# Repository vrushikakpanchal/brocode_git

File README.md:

# UnPlugged 2.0 - Smart City Sentinel

## Overview
This project was developed as part of **UnPlugged 2.0**, a 24-hour hardware hackathon organized by Shri Vile Parle Kelavani Mandal's Dwarkadas J. Sanghvi College of Engineering. Our solution focuses on **AI-driven IoT & GIS-based urban intelligence** to optimize traffic management, environmental monitoring, and public safety.

## Problem Statement
With rapid urbanization, cities face challenges in managing infrastructure, optimizing resources, and ensuring public safety. Existing systems often react too slowly, leading to inefficiencies. Our task was to **engineer an autonomous system** integrating:
- **IoT-based urban monitoring**
- **Multi-sensor data fusion**
- **Geographic Information System (GIS)**
- **AI models for traffic control, emergency response, and environmental monitoring**
- **Decentralized edge AI for real-time decision-making**

## Solution Implemented
### **1. Traffic Flow Optimization** 🚦
- **ESP32 cameras** placed across **4 lanes** to monitor vehicle density.
- AI logic to **prioritize lane clearance** based on congestion levels.

### **2. Environmental Monitoring** 🌍
- Hardware setup includes sensors for **AQI, dust, and temperature levels**.
- Data is **transmitted in real-time** to a **cloud-based dashboard**.

### **3. User Dashboard & Access** 🖥️
- **Two types of logins:**
  - **Admin (Traffic Police):** Controls signal timings.
  - **User:** Accesses live traffic updates and environmental data.
- **Web-based dashboard** for real-time monitoring.

## Tech Stack & Components
- **Hardware:** ESP32-CAM, air quality sensors, temperature sensors, solar-powered PCB
- **Software:** KiCad (PCB design), Python, Flask, React.js
- **Cloud & AI:** Firebase, Edge AI for anomaly detection

## Team Members 👥
- Vrushika Panchal [Diploma - AI/ML]
- Harsh Pandey [B.Tech - EXTC]
- Soham Nagvekar [B.Tech - EXTC]
- Prasad Rane [B.Tech - EXTC]
- Atharva Wadekar [B.Tech - EXTC]
- Advait Shinde [Diploma - AI/ML]

## Repository Structure
```
📂 brocode_git
 ┣ 📂 01_Kicad_PCB        # KiCad PCB designs
 ┣ 📂 02_GERBER           # ESP32 & IoT sensor integration
 ┣ 📂 03_project_images           # React.js frontend for monitoring
 ┣ 📂 04_frontend_website               # Traffic analysis & anomaly detection
 ┣ 📜 README.md               # Project documentation
```

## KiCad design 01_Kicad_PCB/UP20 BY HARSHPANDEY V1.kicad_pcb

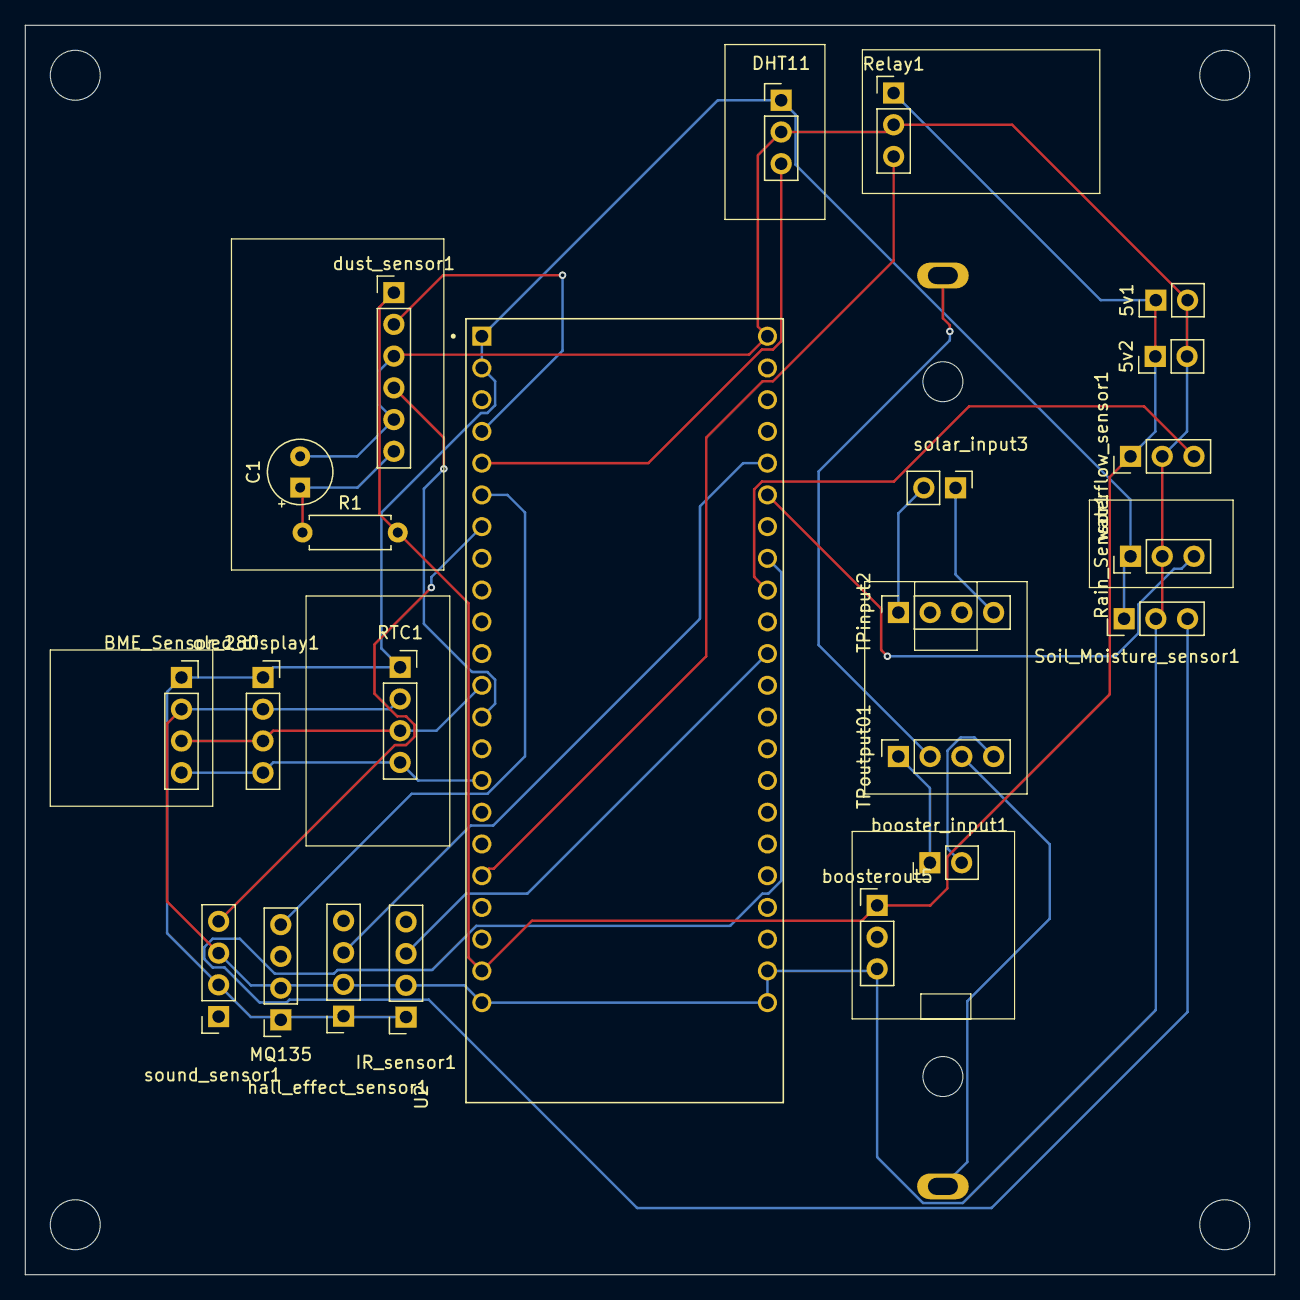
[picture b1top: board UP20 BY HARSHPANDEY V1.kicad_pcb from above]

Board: 2 copper layers, 100.0 x 100.0 mm, 24 parts (1 on the bottom side), 23 nets.

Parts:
5v1, 5v2: Conn_01x02_Pin; PinHeader_1x02_P2.54mm_Vertical
BME_Sensor_280: Conn_01x04_Pin; PinSocket_1x04_P2.54mm_Vertical
BT2: BK-18650-PC2; BAT_BK-18650-PC2
C1: C_Polarized; CP_Radial_Tantal_D5.0mm_P2.50mm
DHT11: Conn_01x03_Pin; PinHeader_1x03_P2.54mm_Vertical
IR_sensor1: Conn_01x04_Pin; PinSocket_1x04_P2.54mm_Vertical
MQ135: Conn_01x04_Pin; PinSocket_1x04_P2.54mm_Vertical
R1: R; R_Axial_DIN0207_L6.3mm_D2.5mm_P7.62mm_Horizontal
RTC1: Conn_01x04_Pin; PinSocket_1x04_P2.54mm_Vertical
Rain_Sensor1: Conn_01x03_Pin; PinHeader_1x03_P2.54mm_Vertical
Relay1: Conn_01x03_Pin; PinHeader_1x03_P2.54mm_Vertical
Soil_Moisture_sensor1: Conn_01x03_Pin; PinHeader_1x03_P2.54mm_Vertical
TPinput2: Conn_01x04_Pin; PinSocket_1x04_P2.54mm_Vertical
TPoutput01: Conn_01x04_Pin; PinSocket_1x04_P2.54mm_Vertical
U2: ESP32-S3-DEVKITC-1-N8R2; XCVR_ESP32-S3-DEVKITC-1-N8R2
booster_input1: Conn_01x02_Pin; PinHeader_1x02_P2.54mm_Vertical
boosterout5: Conn_01x03_Pin; PinHeader_1x03_P2.54mm_Vertical
dust_sensor1: Conn_01x06_Pin; PinHeader_1x06_P2.54mm_Vertical
hall_effect_sensor1: Conn_01x04_Pin; PinSocket_1x04_P2.54mm_Vertical
oled_display1: Conn_01x04_Pin; PinSocket_1x04_P2.54mm_Vertical
solar_input3: Conn_01x02_Pin; PinHeader_1x02_P2.54mm_Vertical
sound_sensor1: Conn_01x04_Pin; PinSocket_1x04_P2.54mm_Vertical
waterflow_sensor1: Conn_01x03_Pin; PinHeader_1x03_P2.54mm_Vertical

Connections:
3.3V: BME_Sensor_280.1, DHT11.1, IR_sensor1.1, MQ135.1, RTC1.1, Rain_Sensor1.1, Soil_Moisture_sensor1.1, U2.J1_1 (3V3), U2.J1_2 (3V3), hall_effect_sensor1.1, oled_display1.1, sound_sensor1.2
5V: 5v1.1, 5v2.1, R1.2, Relay1.1, U2.J1_21 (5V0), boosterout5.1, dust_sensor1.1, waterflow_sensor1.1
GND: 5v1.2, 5v2.2, BME_Sensor_280.2, C1.2, DHT11.2, IR_sensor1.2, MQ135.2, RTC1.2, Rain_Sensor1.2, Relay1.2, Soil_Moisture_sensor1.2, U2.J1_22 (GND), U2.J3_1 (GND), U2.J3_21 (GND), U2.J3_22 (GND), boosterout5.3, dust_sensor1.3, dust_sensor1.5, hall_effect_sensor1.2, oled_display1.2, sound_sensor1.3, waterflow_sensor1.2
unnamed: DHT11.3, U2.J1_5 (GPIO5)
unnamed: IR_sensor1.3, U2.J3_11 (GPIO37)
unnamed: MQ135.4, U2.J1_6 (GPIO6)
unnamed: Rain_Sensor1.3, U2.J3_6 (MTMS/GPIO42)
unnamed: Relay1.3, U2.J1_18 (GPIO12)
unnamed: Soil_Moisture_sensor1.3, U2.J3_8 (MTDO/GPIO40)
unnamed: TPinput2.1, solar_input3.2
unnamed: TPinput2.4, solar_input3.1
unnamed: TPoutput01.1, booster_input1.1
unnamed: BT2.+, TPoutput01.2
unnamed: BT2.-, TPoutput01.3
unnamed: TPoutput01.4, booster_input1.2
unnamed: U2.J3_5 (GPIO2), hall_effect_sensor1.3
unnamed: U2.J1_13 (GPIO3), dust_sensor1.4
unnamed: U2.J1_4 (GPIO4), dust_sensor1.2
unnamed: U2.J1_7 (GPIO7), sound_sensor1.4
unnamed: U2.J3_9 (MTCK/GPIO39), waterflow_sensor1.3
unnamed: C1.1, R1.1, dust_sensor1.6
SCL: BME_Sensor_280.4, RTC1.4, U2.J1_15 (GPIO9), oled_display1.4
SDA: BME_Sensor_280.3, RTC1.3, U2.J1_12 (GPIO8), oled_display1.3

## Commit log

2025-03-11 Removed all existing files
2025-03-11 Ignore large video files
2025-03-11 Added 01_Kicad_PCB
2025-03-11 Added 04_frontend_website
